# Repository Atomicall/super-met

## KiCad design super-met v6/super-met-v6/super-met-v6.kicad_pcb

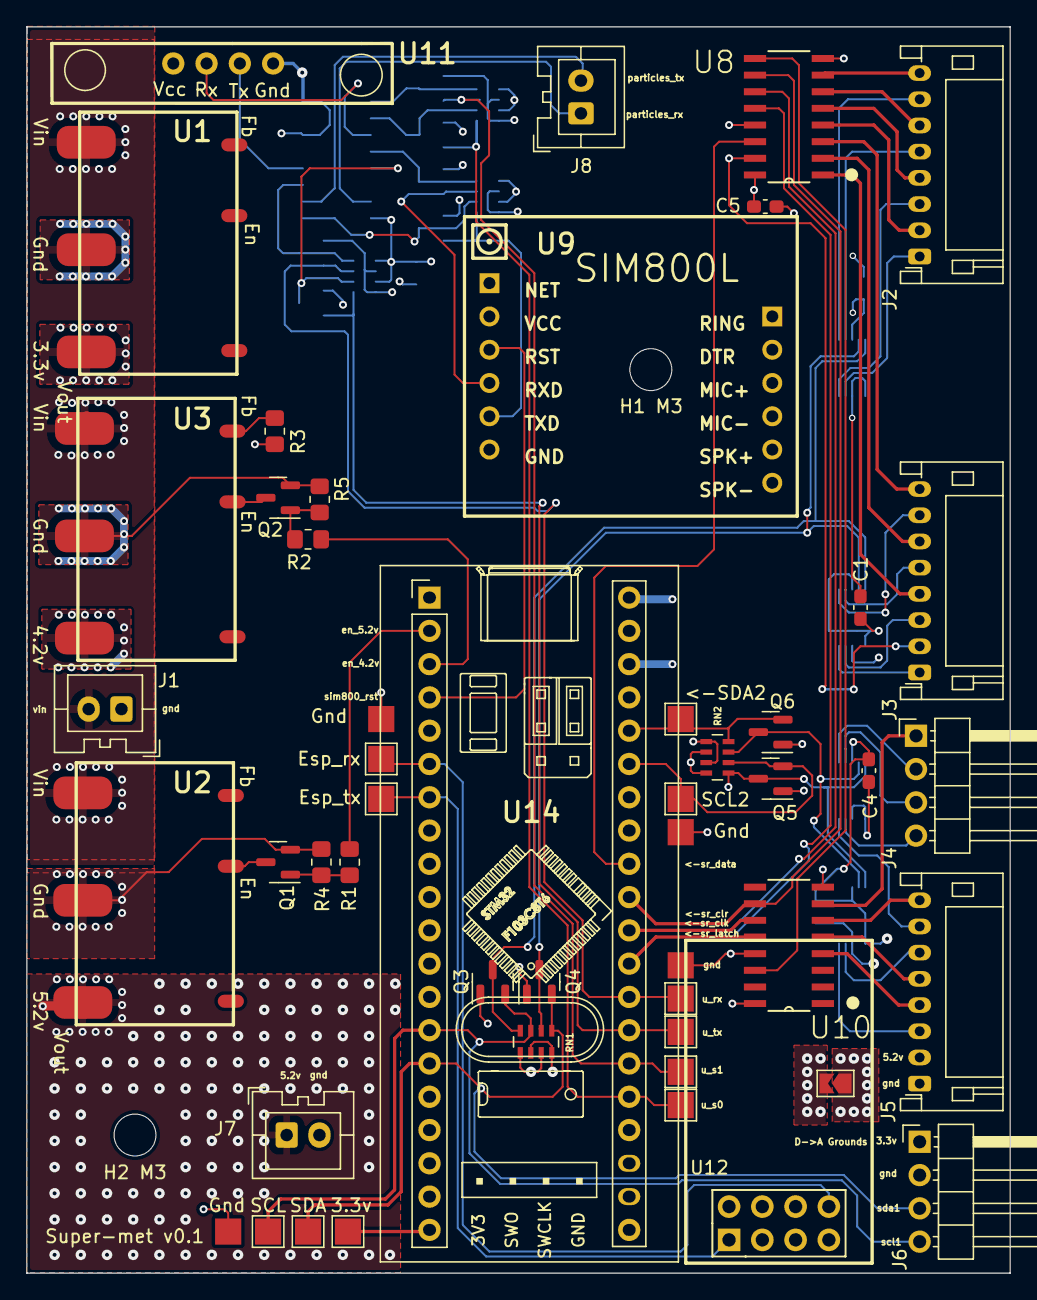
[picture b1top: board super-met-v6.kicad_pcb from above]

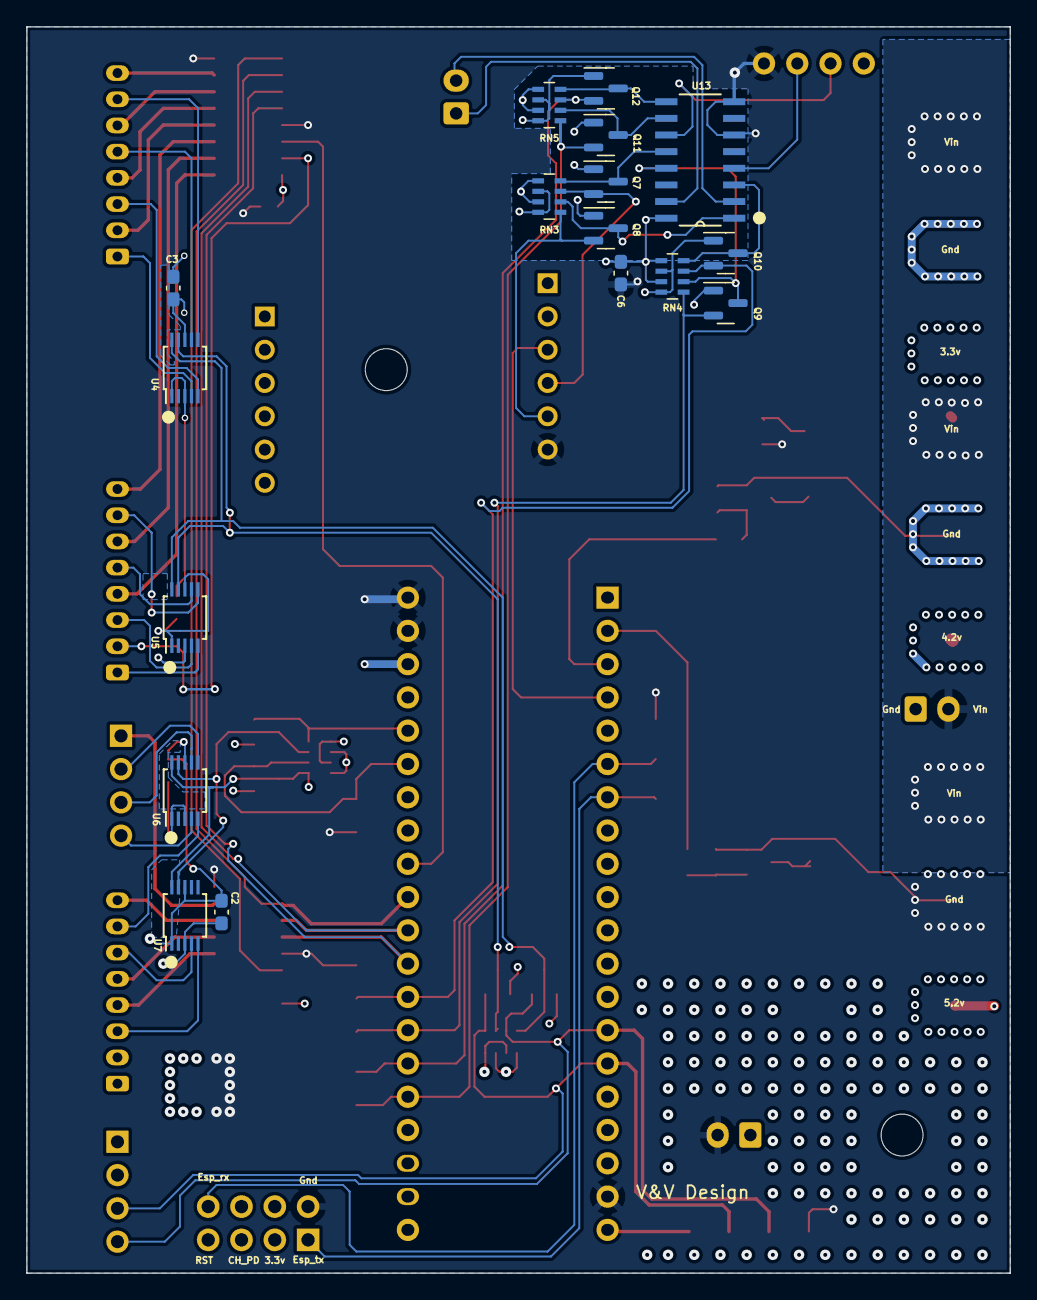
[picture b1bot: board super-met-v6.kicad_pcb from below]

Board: 4 copper layers, 75.1 x 95.1 mm, 64 parts (17 on the bottom side), 70 nets.

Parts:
3.3v: TestPoint; TestPoint_Pad_2.0x2.0mm
<-SDA2: TestPoint; TestPoint_Pad_2.0x2.0mm
C1, C2, C3, C4, C5, C6: 0.1uF; C_0603_1608Metric_Pad1.08x0.95mm_HandSolder
D->A Grounds: Jumper_2_Bridged; SolderJumper-2_P1.3mm_Open_TrianglePad1.0x1.5mm
Esp_rx: TestPoint; TestPoint_Pad_2.0x2.0mm
Esp_tx: TestPoint; TestPoint_Pad_2.0x2.0mm
H1 M3, H2 M3: MountingHole; MountingHole_3.2mm_M3
J1, J7, J8: Conn_01x02; JST_XA_B02B-XASK-1_1x02_P2.50mm_Vertical
J2, J3, J5: Conn_01x08; JST_PH_S8B-PH-K_1x08_P2.00mm_Horizontal
J4, J6: Conn_01x04; PinHeader_1x04_P2.54mm_Horizontal
Q1, Q2, Q3, Q4, Q5, Q6, Q7, Q8, Q9, Q10, Q11, Q12: AO3400A; SOT-23
R1, R2: 100; R_0805_2012Metric_Pad1.20x1.40mm_HandSolder
R3: 16.5-16.7-17k*; R_0805_2012Metric_Pad1.20x1.40mm_HandSolder
R4, R5: 1k; R_0805_2012Metric_Pad1.20x1.40mm_HandSolder
RN1, RN2, RN3, RN4, RN5: R_Pack04; R_Array_Concave_4x0603
SCL, SCL2: TestPoint; TestPoint_Pad_2.0x2.0mm
SDA: TestPoint; TestPoint_Pad_2.0x2.0mm
U1, U2, U3: DC-DC_MOD; DC-DC
U4, U5, U6, U7: ADS1115IDGS; TSSOP-10_3x3mm_P0.5mm
U8, U10: 74HC595; SOIC127P600X175-16N
U9: SIM800L
U11: GY-GPS6MV2
U12: ESP-01v090; ESP-01
U13: 74HC4052D; SOIC127P600X175-16N
U14: BLUEPILL
u_rx: TestPoint; TestPoint_Pad_2.0x2.0mm
u_s0, u_s1: TestPoint; TestPoint_Pad_2.0x2.0mm
u_tx: TestPoint; TestPoint_Pad_2.0x2.0mm

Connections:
3.3v: 3.3v.1, C5.1, J6.1, Q3.1 (G), Q4.1 (G), Q5.1 (G), Q6.1 (G), Q7.1 (G), Q8.1 (G), Q9.1 (G), Q10.1 (G), Q11.1 (G), Q12.1 (G), RN1.2 (R2.1), RN1.4 (R4.1), RN2.1 (R1.1), RN2.3 (R3.1), RN3.6 (R3.2), RN3.8 (R1.2), RN4.6 (R3.2), RN4.8 (R1.2), RN5.6 (R3.2), RN5.8 (R1.2), U1.3 (Vout), U8.16 (VCC), U10.16 (VCC), U12.3 (CH_PD), U12.5 (RST), U12.7 (VCC), U14.20 (3V3), U14.38 (3V3)
4.2v: U3.3 (Vout), U9.2 (Vcc)
5.2v: C1.1, C2.1, C3.1, C4.1, C6.1, J5.2, J7.1, RN1.1 (R1.1), RN1.3 (R3.1), RN2.2 (R2.1), RN2.4 (R4.1), RN3.5 (R4.2), RN3.7 (R2.2), RN4.5 (R4.2), RN4.7 (R2.2), RN5.5 (R4.2), RN5.7 (R2.2), U2.3 (Vout), U4.8 (VDD), U5.1 (ADDR), U5.8 (VDD), U6.8 (VDD), U7.1 (ADDR), U7.8 (VDD), U11.1 (Vin), U13.16 (VCC)
/Power_Vin: J1.2, U1.1 (Vin), U2.1 (Vin), U3.1 (Vin)
/SCL1: J6.4, Q3.2 (S), RN1.7 (R2.2), SCL.1, U14.14 (PB6)
/SCL2: Q5.2 (S), RN2.6 (R3.2), SCL2.1, U14.35 (PB10)
/SDA1: J6.3, Q4.2 (S), RN1.5 (R4.2), SDA.1, U14.15 (PB7)
/SDA2: <-SDA2.1, Q6.2 (S), RN2.8 (R1.2), U14.36 (PB11)
/en_4.2v: Q2.3 (D), U3.5 (En)
/en_4.2v_signal: R2.1, U14.3 (PB14)
/en_5.2v: Q1.3 (D), U2.5 (En)
/en_5.2v_signal: R1.1, U14.2 (PB13)
/esp_rx: Esp_rx.1, U12.8 (URXD), U14.6 (PA9)
/esp_tx: Esp_tx.1, U12.1 (UTXD), U14.7 (PA10)
/gps_rx: U11.2 (Rx), U13.11 (1Y3)
/gps_tx: U11.3 (Tx), U13.4 (2Y3)
/particles_rx: J8.1, U13.15 (1Y2)
/particles_tx: J8.2, U13.2 (2Y2)
/s1_en_1: J2.2, U8.4 (QE)
/s1_out_1: J2.1, U4.4 (AIN0)
/s2_en_1: J2.4, U8.5 (QF)
/s2_out_1: J2.3, U4.5 (AIN1)
/s3_en_1: J2.6, U8.6 (QG)
/s3_out_1: J2.5, U4.7 (AIN3)
/s4_en_1: J2.8, U8.7 (QH)
/s4_out_1: J2.7, U4.6 (AIN2)
/s5_en_1: J3.2, U8.15 (QA)
/s5_out_1: J3.1, U5.5 (AIN1)
/s6_en_1: J3.4, U8.1 (QB)
/s6_out_1: J3.3, U5.4 (AIN0)
/s7_en_1: J3.6, U8.2 (QC)
/s7_out_1: J3.5, U5.7 (AIN3)
/s8_en_1: J3.8, U8.3 (QD)
/s8_out_1: J3.7, U5.6 (AIN2)
/s9_en_1: J5.4, U10.4 (QE)
/s9_out_1: J5.3, U7.5 (AIN1)
/s10_en_1: J5.5, U10.5 (QF)
/s10_out_1: J5.6, U7.4 (AIN0)
/s11_12_13_en_1: J4.1, U10.7 (QH)
/s11_out_1: J4.4, U6.4 (AIN0)
/s12_out_1: J4.3, U6.7 (AIN3)
/s13_out_1: J4.2, U6.6 (AIN2)
/s14_en_1: J5.8, U10.6 (QG)
/sim800_rst: U9.3 (Rst), U14.4 (PB15)
/sim800_rx: Q7.3 (D), RN3.4 (R4.1), U13.12 (1Y0)
/sim800_tx: Q8.3 (D), RN3.2 (R2.1), U13.1 (2Y0)
/sr_clear: U8.10 (~SRCLR), U10.10 (~SRCLR), U14.31 (PA6)
/sr_clk: U8.11 (SRCLK), U10.11 (SRCLK), U14.30 (PA5)
/sr_in: U8.14 (SER), U14.32 (PA7)
/sr_latch: U8.12 (RCLK), U10.12 (RCLK), U14.29 (PA4)
/uart_mux_rx: Q10.2 (S), RN4.3 (R3.1), U14.28 (PA3), u_rx.1
/uart_mux_s0: Q11.2 (S), RN5.1 (R1.1), U14.25 (PA0), u_s0.1
/uart_mux_s1: Q12.2 (S), RN5.3 (R3.1), U14.26 (PA1), u_s1.1
/uart_mux_tx: Q9.2 (S), RN4.1 (R1.1), U14.27 (PA2), u_tx.1
GND: C5.2, C6.2, D->A Grounds.2 (B), J1.1, J7.2, Q1.2 (S), Q2.2 (S), R3.2, R4.2, R5.2, U1.2 (Gnd), U2.2 (Gnd), U3.2 (Gnd), U8.8 (GND), U8.13 (~OE), U9.6 (Gnd), U10.8 (GND), U10.13 (~OE), U11.4 (Gnd), U12.2 (GND), U13.6 (~E), U13.8 (GND), U14.19 (GND), U14.39 (GND), U14.40 (GND)
GND3: C1.2, C2.2, C3.2, C4.2, D->A Grounds.1 (A), J5.1, J6.2, U4.1 (ADDR), U4.3 (GND), U5.3 (GND), U6.1 (ADDR), U6.3 (GND), U7.3 (GND)
unnamed: Q1.1 (G), R1.2, R4.1
unnamed: Q2.1 (G), R2.2, R5.1
unnamed: Q3.3 (D), RN1.8 (R1.2), U4.10 (SCL), U5.10 (SCL)
unnamed: Q4.3 (D), RN1.6 (R3.2), U4.9 (SDA), U5.9 (SDA)
unnamed: Q5.3 (D), RN2.5 (R4.2), U6.10 (SCL), U7.10 (SCL)
unnamed: Q6.3 (D), RN2.7 (R2.2), U6.9 (SDA), U7.9 (SDA)
unnamed: Q7.2 (S), RN3.3 (R3.1), U9.4 (Rx)
unnamed: Q8.2 (S), RN3.1 (R1.1), U9.5 (Tx)
unnamed: Q9.3 (D), RN4.2 (R2.1), U13.13 (1Z)
unnamed: Q10.3 (D), RN4.4 (R4.1), U13.3 (2Z)
unnamed: Q11.3 (D), RN5.2 (R2.1), U13.10 (S0)
unnamed: Q12.3 (D), RN5.4 (R4.1), U13.9 (S1)
unnamed: R3.1, U3.6 (Fb)
unnamed: U8.9 (QH'), U10.14 (SER)

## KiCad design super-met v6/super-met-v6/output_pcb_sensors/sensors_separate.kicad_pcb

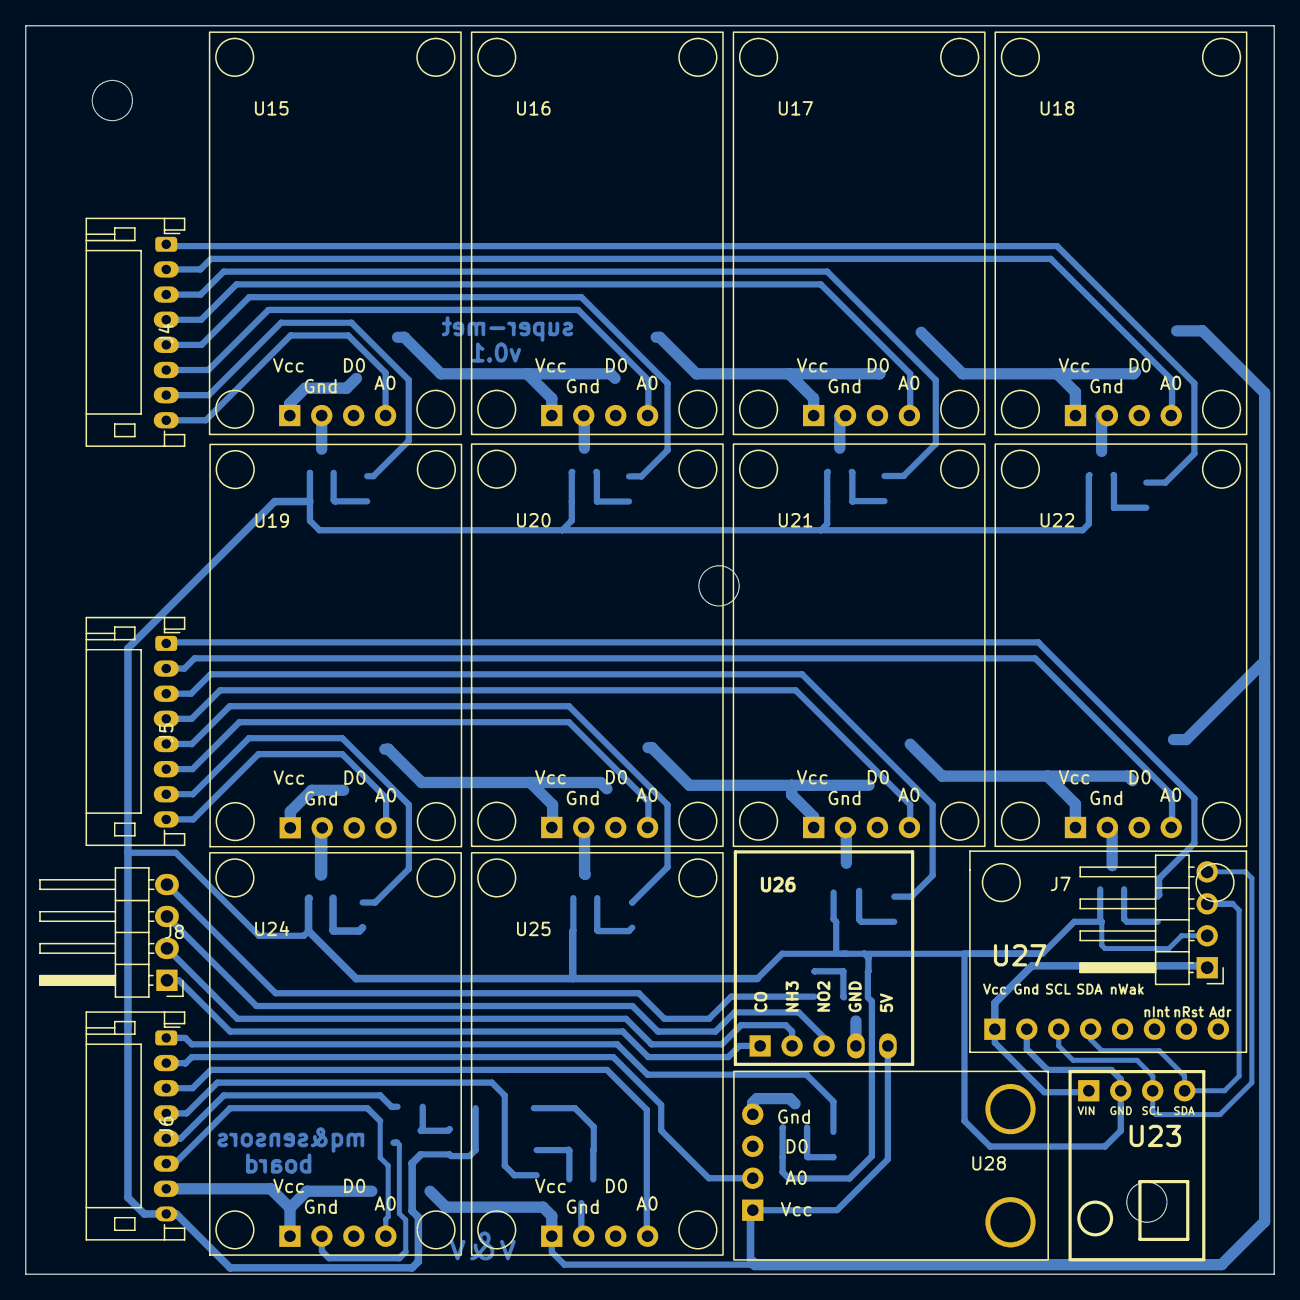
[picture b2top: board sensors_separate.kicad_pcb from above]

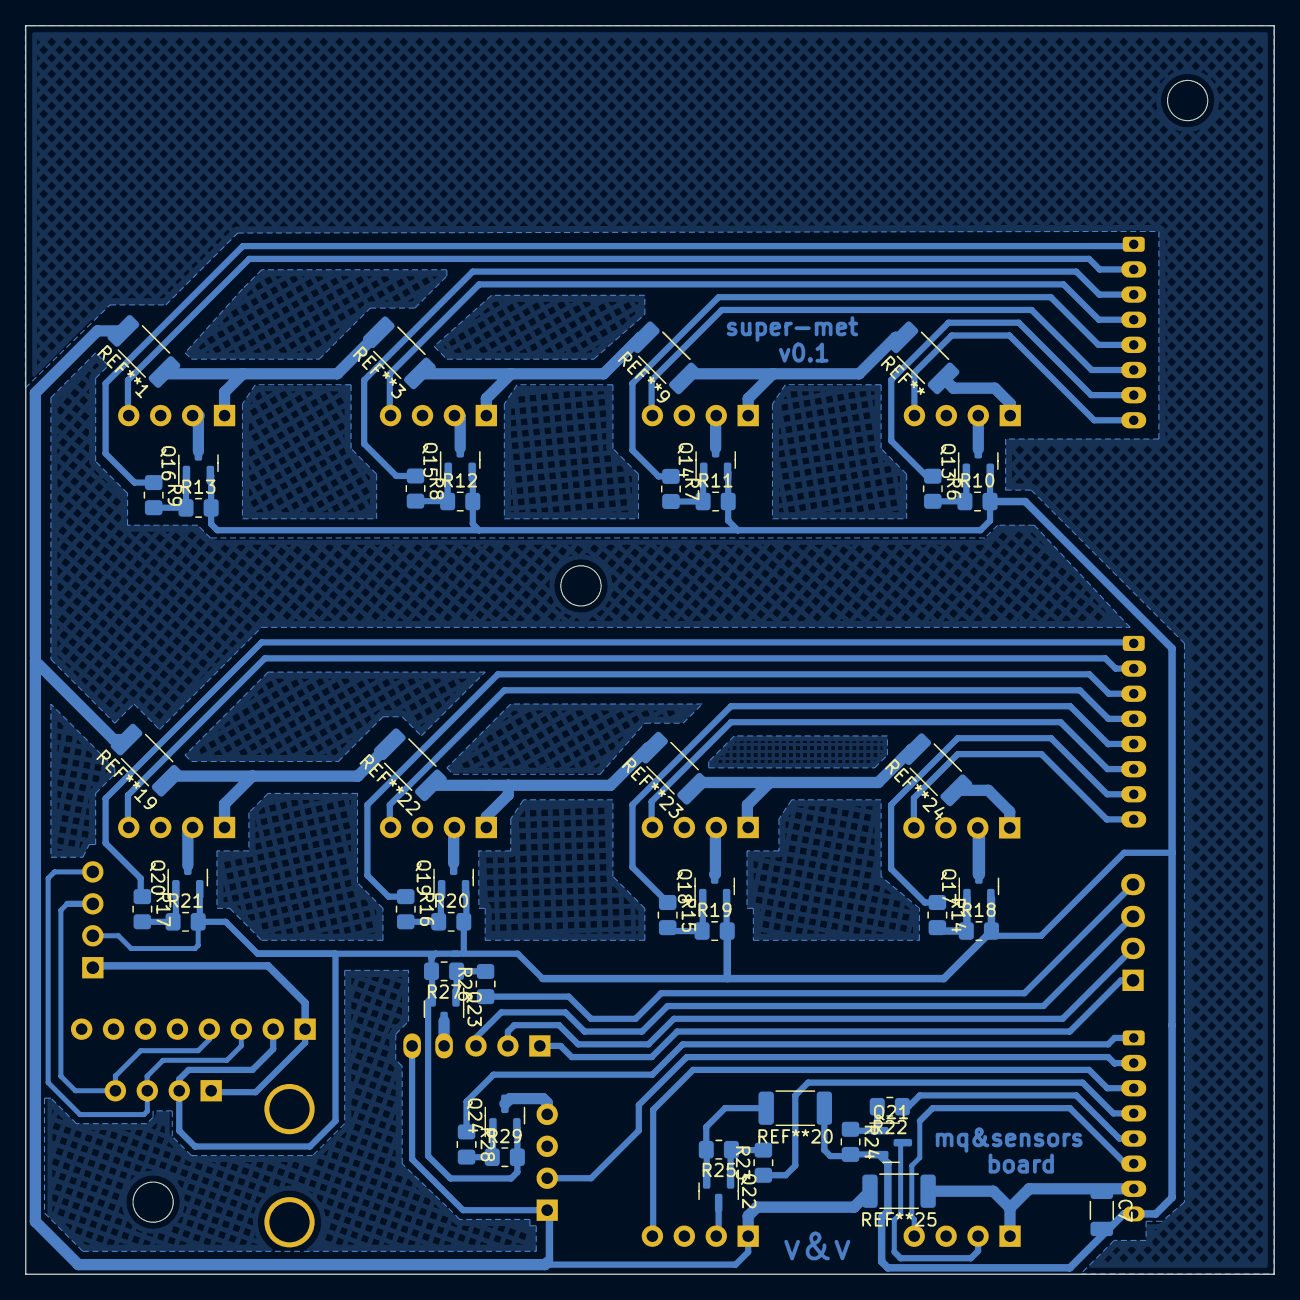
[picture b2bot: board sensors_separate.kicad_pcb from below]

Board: 2 copper layers, 99.3 x 99.3 mm, 57 parts (37 on the bottom side), 55 nets.

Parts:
C7: 10uF; C_1206_3216Metric
H2: MountingHole; MountingHole_3.2mm_M3
J4, J5, J6: Conn_01x08; JST_PH_S8B-PH-K_1x08_P2.00mm_Horizontal
J7, J8: Conn_01x04; PinHeader_1x04_P2.54mm_Horizontal
Q13, Q14, Q15, Q16, Q17, Q18, Q19, Q20, Q21, Q22, Q23, Q24: AO3400A; SOT-23
R6, R7, R8, R9, R14, R15, R16, R17, R22, R23, R26, R28: 100; R_0805_2012Metric_Pad1.20x1.40mm_HandSolder
R10, R11, R12, R13, R18, R19, R20, R21, R24, R25, R27, R29: 1k; R_0805_2012Metric_Pad1.20x1.40mm_HandSolder
U15, U16, U17, U18, U19, U20, U21, U22, U24, U25: MQ GENERIC BOARD SENSOR; MQ BLUE GENERIC MODULE
U23: AHT10 MODULE; AHT10 FOOT PRINT
U26: MICS-6814
U27: CCS811
U28: MS-1100

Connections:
Board_0-/Sensors/3.3v_conn: J7.1, U23.4 (Vin), U27.1 (Vcc)
Board_0-/Sensors/5.2v: C7.1, J6.7, U15.1 (Vcc), U16.1 (Vcc), U17.1 (Vcc), U18.1 (Vcc), U19.1 (Vcc), U20.1 (Vcc), U21.1 (Vcc), U22.1 (Vcc), U24.1 (Vcc), U25.1 (Vcc), U26.5 (Vin), U28.1 (Vin)
Board_0-/Sensors/s1_en: J4.7, R6.1
Board_0-/Sensors/s1_out: J4.8, U15.4 (A0)
Board_0-/Sensors/s2_en: J4.5, R7.1
Board_0-/Sensors/s2_out: J4.6, U16.4 (A0)
Board_0-/Sensors/s3_en: J4.3, R8.1
Board_0-/Sensors/s3_out: J4.4, U17.4 (A0)
Board_0-/Sensors/s4_en: J4.1, R9.1
Board_0-/Sensors/s4_out: J4.2, U18.4 (A0)
Board_0-/Sensors/s5_en: J5.7, R14.1
Board_0-/Sensors/s5_out: J5.8, U19.4 (A0)
Board_0-/Sensors/s6_en: J5.5, R15.1
Board_0-/Sensors/s6_out: J5.6, U20.4 (A0)
Board_0-/Sensors/s7_en: J5.3, R16.1
Board_0-/Sensors/s7_out: J5.4, U21.4 (A0)
Board_0-/Sensors/s8_en: J5.1, R17.1
Board_0-/Sensors/s8_out: J5.2, U22.4 (A0)
Board_0-/Sensors/s9_en: J6.5, R22.1
Board_0-/Sensors/s9_out: J6.6, U24.4 (A0)
Board_0-/Sensors/s10_en: J6.4, R23.1
Board_0-/Sensors/s10_out: J6.3, U25.4 (A0)
Board_0-/Sensors/s11_12_13_en: J8.4, R26.1
Board_0-/Sensors/s11_out: J8.1, U26.1 (CO)
Board_0-/Sensors/s12_out: J8.2, U26.2 (NH3)
Board_0-/Sensors/s13_out: J8.3, U26.3 (NO2)
Board_0-/Sensors/s14_en: J6.1, R28.1
Board_0-/Sensors/s14_out: J6.2, U28.2 (Signal)
Board_0-/Sensors/scl: J7.4, U23.2 (SCL), U27.3 (Scl)
Board_0-/Sensors/sda: J7.3, U23.1 (SDA), U27.4 (Sda)
Board_0-GND2: C7.2, J6.8, J7.2, Q13.2 (S), Q14.2 (S), Q15.2 (S), Q16.2 (S), Q17.2 (S), Q18.2 (S), Q19.2 (S), Q20.2 (S), Q21.2 (S), Q22.2 (S), Q23.2 (S), Q24.2 (S), R10.2, R11.2, R12.2, R13.2, R18.2, R19.2, R20.2, R21.2, R24.2, R25.2, R27.2, R29.2, U23.3 (Gnd), U27.2 (Gnd)
Board_0-Net-(Q13-Pad1): Q13.1 (G), R6.2, R10.1
Board_0-Net-(Q13-Pad3): Q13.3 (D), U15.2 (Gnd)
Board_0-Net-(Q14-Pad1): Q14.1 (G), R7.2, R11.1
Board_0-Net-(Q14-Pad3): Q14.3 (D), U16.2 (Gnd)
Board_0-Net-(Q15-Pad1): Q15.1 (G), R8.2, R12.1
Board_0-Net-(Q15-Pad3): Q15.3 (D), U17.2 (Gnd)
Board_0-Net-(Q16-Pad1): Q16.1 (G), R9.2, R13.1
Board_0-Net-(Q16-Pad3): Q16.3 (D), U18.2 (Gnd)
Board_0-Net-(Q17-Pad1): Q17.1 (G), R14.2, R18.1
Board_0-Net-(Q17-Pad3): Q17.3 (D), U19.2 (Gnd)
Board_0-Net-(Q18-Pad1): Q18.1 (G), R15.2, R19.1
Board_0-Net-(Q18-Pad3): Q18.3 (D), U20.2 (Gnd)
Board_0-Net-(Q19-Pad1): Q19.1 (G), R16.2, R20.1
Board_0-Net-(Q19-Pad3): Q19.3 (D), U21.2 (Gnd)
Board_0-Net-(Q20-Pad1): Q20.1 (G), R17.2, R21.1
Board_0-Net-(Q20-Pad3): Q20.3 (D), U22.2 (Gnd)
Board_0-Net-(Q21-Pad1): Q21.1 (G), R22.2, R24.1
Board_0-Net-(Q21-Pad3): Q21.3 (D), U24.2 (Gnd)
Board_0-Net-(Q22-Pad1): Q22.1 (G), R23.2, R25.1
Board_0-Net-(Q22-Pad3): Q22.3 (D), U25.2 (Gnd)
Board_0-Net-(Q23-Pad1): Q23.1 (G), R26.2, R27.1
Board_0-Net-(Q23-Pad3): Q23.3 (D), U26.4 (Gnd)
Board_0-Net-(Q24-Pad1): Q24.1 (G), R28.2, R29.1
Board_0-Net-(Q24-Pad3): Q24.3 (D), U28.4 (Gnd)

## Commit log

2023-01-09 altium temp
2023-01-09 schema 1
2023-01-16 adding v6 (libst included and ported))
2023-01-17 main scheme:
2023-01-20 sensors board
2023-01-24 board in progress
2023-01-25 board in progress1
2023-01-29 in progress
2023-02-02 before fill
2023-02-03 filling
2023-02-03 filled
2023-02-04 minor pcb fixes
2023-02-07 preparing sensors board
2023-02-08 main dc footprint edited
2023-02-09 4 layer init
2023-02-10 before rearrange
2023-02-14 almost done?
2023-02-15 almost done ?
2023-03-02 before_changing_fills
2023-03-03 ready for order
